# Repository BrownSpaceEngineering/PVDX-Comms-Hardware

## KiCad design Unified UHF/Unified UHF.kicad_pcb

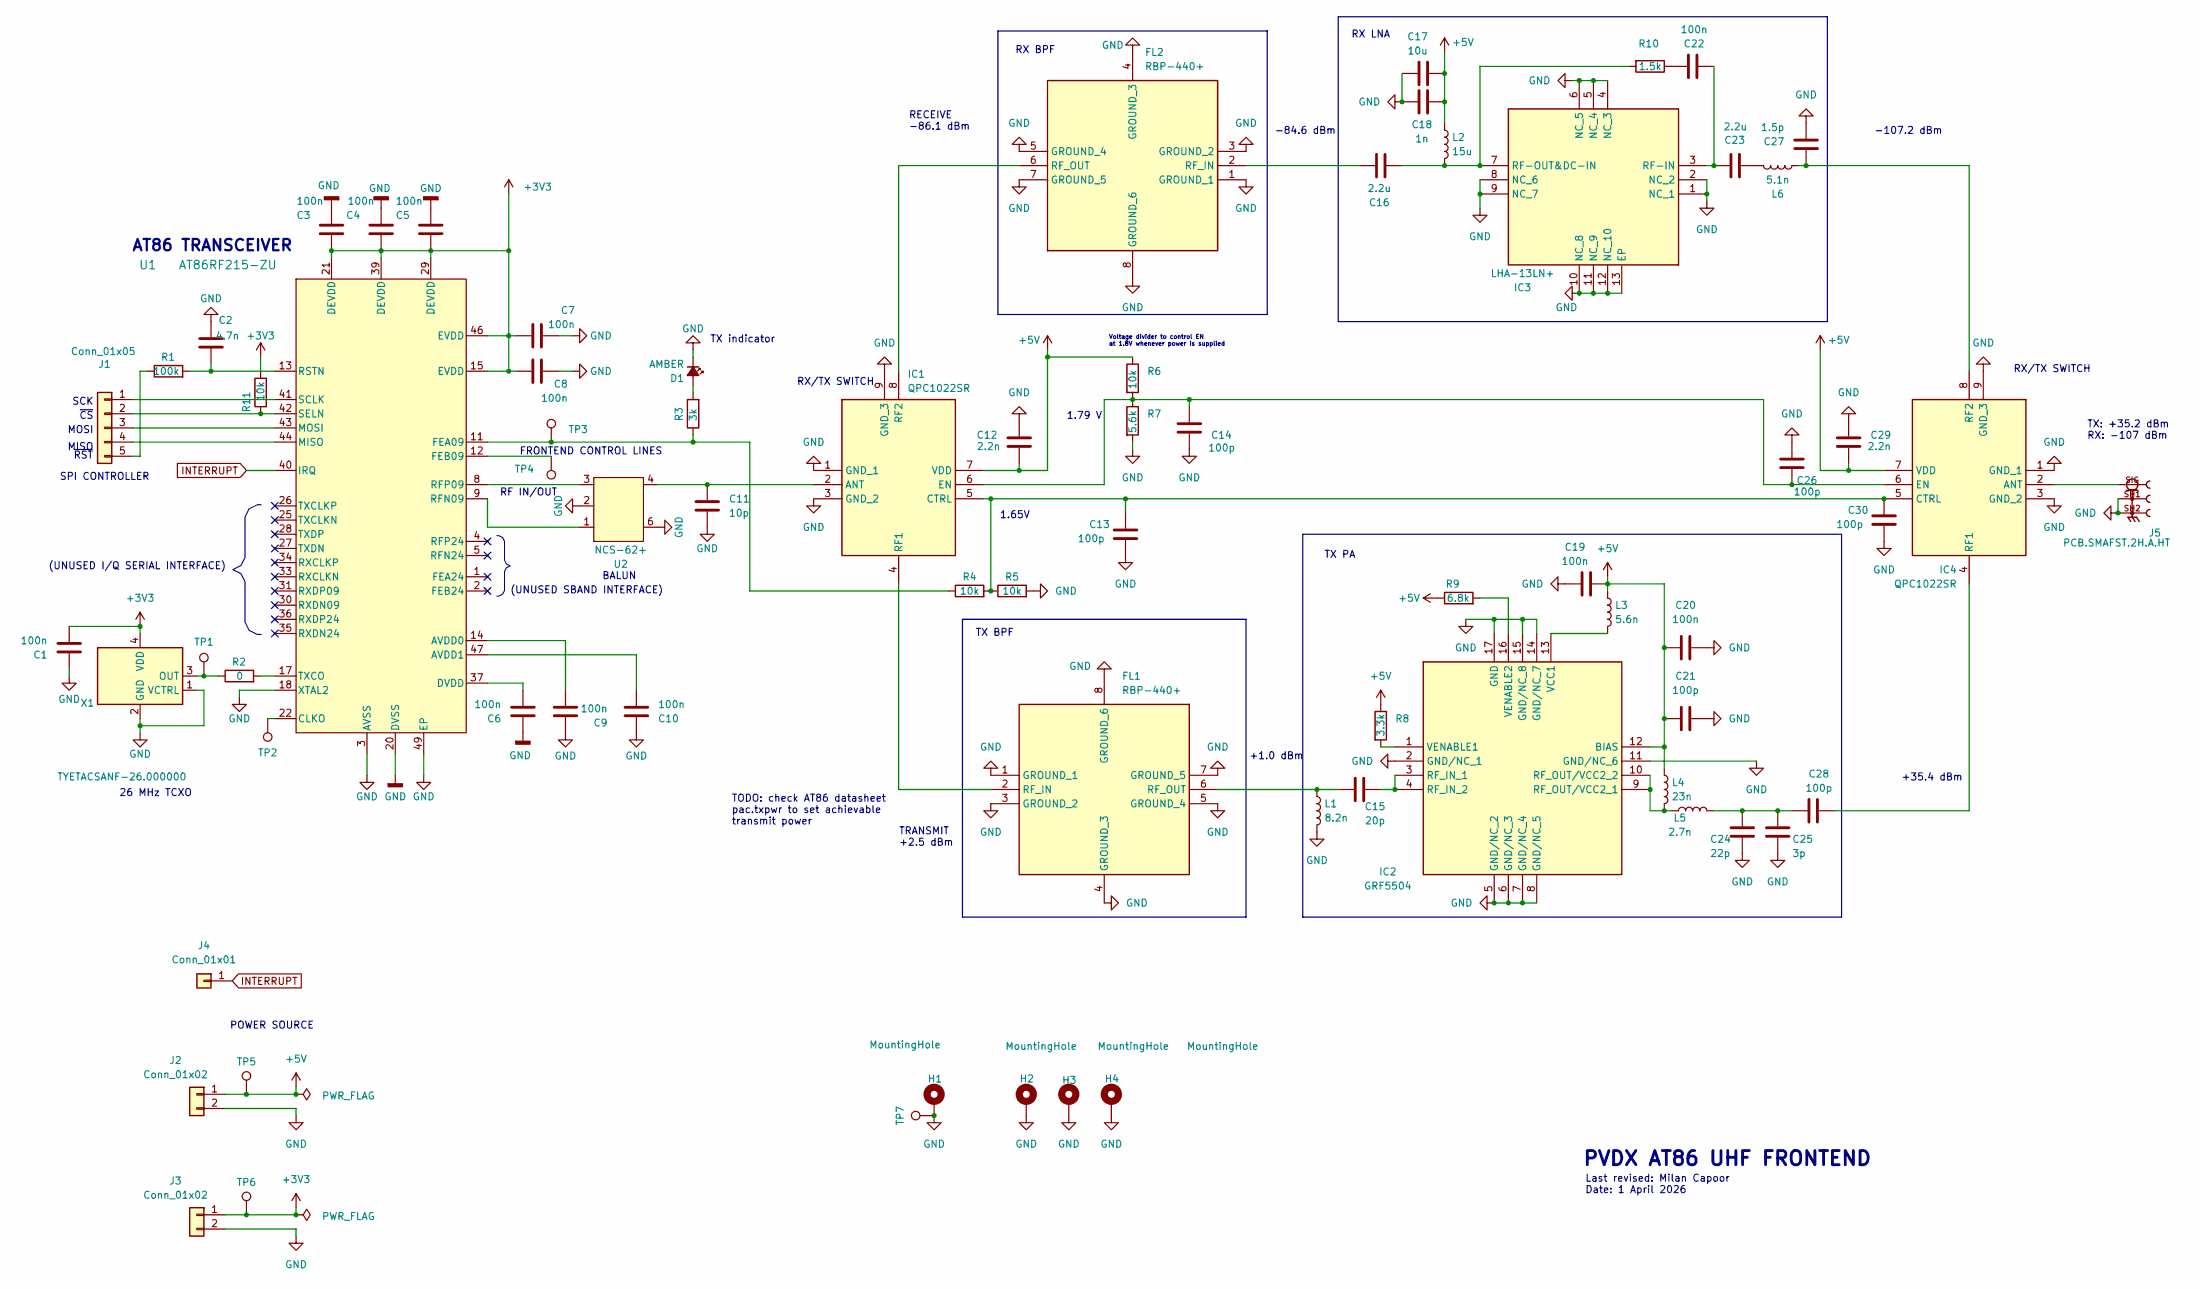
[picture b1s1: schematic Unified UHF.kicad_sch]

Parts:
C1, C3, C4, C5, C6, C7, C8, C9, C10, C19, C20, C22: 100n; C_0603_1608Metric
C2: 4.7n; C_0603_1608Metric
C11: 10p; C_0603_1608Metric
C12, C29: 2.2n; C_0603_1608Metric
C13, C14, C21, C26, C28, C30: 100p; C_0603_1608Metric
C15: 20p; C_0603_1608Metric
C16, C23: 2.2u; C_0603_1608Metric
C17: 10u; C_0805_2012Metric
C18: 1n; C_0603_1608Metric
C24: 22p; C_0603_1608Metric
C25: 3p; C_0603_1608Metric
C27: 1.5p; C_0603_1608Metric
D1: AMBER; LED_0603_1608Metric; MPN 150060AS75000
FL1, FL2: RBP-440+; RBP440; Mouser Part Number 139-RBP-440
H1, H2, H3, H4: MountingHole; MountingHole_3.4mm_Pad(edited from 3.5mm hole)
IC1, IC4: QPC1022SR; Mouser Part Number 772-QPC1022SR
IC2: GRF5504; GR5504; Mouser Part Number 459-GRF5504
IC3: LHA-13LN+; LHA13LN; Mouser Part Number 139-LHA-13LN
J1: Conn_01x05; PinSocket_1x05_P2.54mm_Vertical
J2, J3: Conn_01x02; PinSocket_1x02_P2.54mm_Vertical
J4: Conn_01x01; PinSocket_1x01_P2.54mm_Vertical
J5: PCB.SMAFST.2H.A.HT; TAOGLAS_PCB.SMAFST.2H.A.HT; PARTREV SPE-12-8-140/A/WY; DigiKey_Part_Number 931-1178-ND
L1: 8.2n; L_0603_1608Metric
L2: 15u; L_1210_3225Metric
L3: 5.6n; L_0805_2012Metric
L4: 23n; L_0805_2012Metric
L5: 2.7n; L_0603_1608Metric
L6: 5.1n; L_0603_1608Metric
R1: 100k; R_0603_1608Metric
R2: 0; R_0603_1608Metric
R3: 3k; R_0603_1608Metric
R4, R5, R6, R11: 10k; R_0603_1608Metric
R7: 5.6k; R_0603_1608Metric
R8: 3.3k; R_0603_1608Metric
R9: 6.8k; R_0603_1608Metric
R10: 1.5k; R_0603_1608Metric
TP1, TP2, TP3, TP4, TP5, TP6: TestPoint; TestPoint_Pad_D1.0mm
TP7: TestPoint; TestPoint_THTPad_D1.5mm_Drill0.7mm
U1: AT86RF215-ZU; AT86Footprint
U2: NCS-62+; NCS262
X1: TYETACSANF-26.000000; X_TCXO_SMD_Taitien_2.5x2.0mm; MPN TYETACSANF-26.000000

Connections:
+3V3: C1.2, C3.2, C4.2, C5.2, C7.2, C8.2, J3.1, R11.2, TP6.1 (1_1), U1.15 (EVDD), U1.21 (DEVDD), U1.29 (DEVDD), U1.39 (DEVDD), U1.46 (EVDD), X1.4 (VDD)
+5V: C12.1, C17.1, C18.1, C19.2, C20.1, C21.1, C29.1, IC1.7 (VDD), IC2.12 (BIAS), IC4.7 (VDD), J2.1, L2.1, L3.1, L4.1, R6.1, R8.1, R9.1, TP5.1 (1_1)
GND: C1.1, C2.1, C3.1, C4.1, C5.1, C6.1, C7.1, C8.1, C9.1, C10.1, C11.1, C12.2, C13.2, C14.2, C17.2, C18.2, C19.1, C20.2, C21.2, C24.2, C25.2, C26.2, C27.2, C29.2, C30.2, D1.1 (K), FL1.1 (GROUND_1), FL1.3 (GROUND_2), FL1.4 (GROUND_3), FL1.5 (GROUND_4), FL1.7 (GROUND_5), FL1.8 (GROUND_6), FL2.1 (GROUND_1), FL2.3 (GROUND_2), FL2.4 (GROUND_3), FL2.5 (GROUND_4), FL2.7 (GROUND_5), FL2.8 (GROUND_6), H1.1 (1_1), H2.1 (1_1), H3.1 (1_1), H4.1 (1_1), IC1.1 (GND_1), IC1.3 (GND_2), IC1.9 (GND_3), IC2.2 (GND/NC_1), IC2.5 (GND/NC_2), IC2.6 (GND/NC_3), IC2.7 (GND/NC_4), IC2.8 (GND/NC_5), IC2.11 (GND/NC_6), IC2.14 (GND/NC_7), IC2.15 (GND/NC_8), IC2.17 (GND), IC3.1 (NC_1), IC3.2 (NC_2), IC3.4 (NC_3), IC3.5 (NC_4), IC3.6 (NC_5), IC3.8 (NC_6), IC3.9 (NC_7), IC3.10 (NC_8), IC3.11 (NC_9), IC3.12 (NC_10), IC3.13 (EP), IC4.1 (GND_1), IC4.3 (GND_2), IC4.9 (GND_3), J2.2, J3.2, J5.SH1, J5.SH2, L1.2, R5.2, R7.2, TP7.1 (1_1), U1.3 (AVSS), U1.6 (AVSS), U1.7 (AVSS), U1.10 (AVSS), U1.16 (AVSS), U1.18 (XTAL2), U1.19 (AVSS), U1.20 (DVSS), U1.23 (DVSS), U1.24 (DVSS), U1.32 (DVSS), U1.38 (DVSS), U1.45 (AVSS), U1.48 (AVSS), U1.49 (EP), U2.2, U2.6, X1.1 (VCTRL), X1.2 (GND)
INTERRUPT: J4.1 (Pin_1_1), U1.40 (IRQ)
unnamed: C22.2, R10.1
unnamed: C23.1, L6.2
unnamed: C24.1, C25.1, C28.1, L5.2
unnamed: D1.2 (A), R3.2
unnamed: FL1.2 (RF_IN), IC1.4 (RF1)
unnamed: C15.1, FL1.6 (RF_OUT), L1.1
unnamed: C16.2, FL2.2 (RF_IN)
unnamed: FL2.6 (RF_OUT), IC1.8 (RF2)
unnamed: C11.2, IC1.2 (ANT), U2.4
unnamed: C13.1, C30.1, IC1.5 (CTRL), IC4.5 (CTRL), R4.2, R5.1
unnamed: C14.1, C26.1, IC1.6 (EN), IC4.6 (EN), R6.2, R7.1
unnamed: C15.2, IC2.3 (RF_IN_1), IC2.4 (RF_IN_2)
unnamed: IC2.9 (RF_OUT/VCC2_1), IC2.10 (RF_OUT/VCC2_2), L4.2, L5.1
unnamed: IC2.13 (VCC1), L3.2
unnamed: IC2.1 (VENABLE1), R8.2
unnamed: IC2.16 (VENABLE2), R9.2
unnamed: C22.1, C23.2, IC3.3 (RF-IN)
unnamed: C16.1, IC3.7 (RF-OUT&DC-IN), L2.2, R10.2
unnamed: IC4.2 (ANT), J5.SIG
unnamed: C28.2, IC4.4 (RF1)
unnamed: C27.1, IC4.8 (RF2), L6.1
unnamed: J1.1, U1.41 (SCLK)
unnamed: J1.2, R11.1, U1.42 (SELN)
unnamed: J1.3, U1.43 (MOSI)
unnamed: J1.4, U1.44 (MISO)
unnamed: J1.5, R1.1
unnamed: C9.2, U1.14 (AVDD0)
unnamed: C10.2, U1.47 (AVDD1)
unnamed: TP2.1 (1_1), U1.22 (CLKO)
unnamed: C6.2, U1.37 (DVDD)
unnamed: R3.1, R4.1, TP3.1 (1_1), U1.11 (FEA09)
unnamed: TP4.1 (1_1), U1.12 (FEB09)
unnamed: U1.9 (RFN09), U2.1
unnamed: U1.8 (RFP09), U2.3
unnamed: C2.2, R1.2, U1.13 (RSTN)
unnamed: R2.2, U1.17 (TXCO)
unnamed: R2.1, TP1.1 (1_1), X1.3 (OUT)

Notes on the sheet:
SCK
(UNUSED SBAND INTERFACE)
MISO
TX PA
RX BPF
~{CS}
FRONTEND CONTROL LINES
RX/TX SWITCH
BALUN
SPI CONTROLLER
TRANSMIT +2.5 dBm
TX BPF
+35.4 dBm
-107.2 dBm
-84.6 dBm
1.65V
~{RST}
TX indicator
TODO: check AT86 datasheet pac.txpwr to set achievable transmit power
1.79 V
RF IN/OUT
RECEIVE -86.1 dBm
Last revised: Milan Capoor Date: 1 April 2026
RX LNA
26 MHz TCXO
Voltage divider to control EN at 1.8V whenever power is supplied
(UNUSED I/Q SERIAL INTERFACE)
+1.0 dBm
AT86 TRANSCEIVER
MOSI
PVDX AT86 UHF FRONTEND
POWER SOURCE
TX: +35.2 dBm RX: -107 dBm

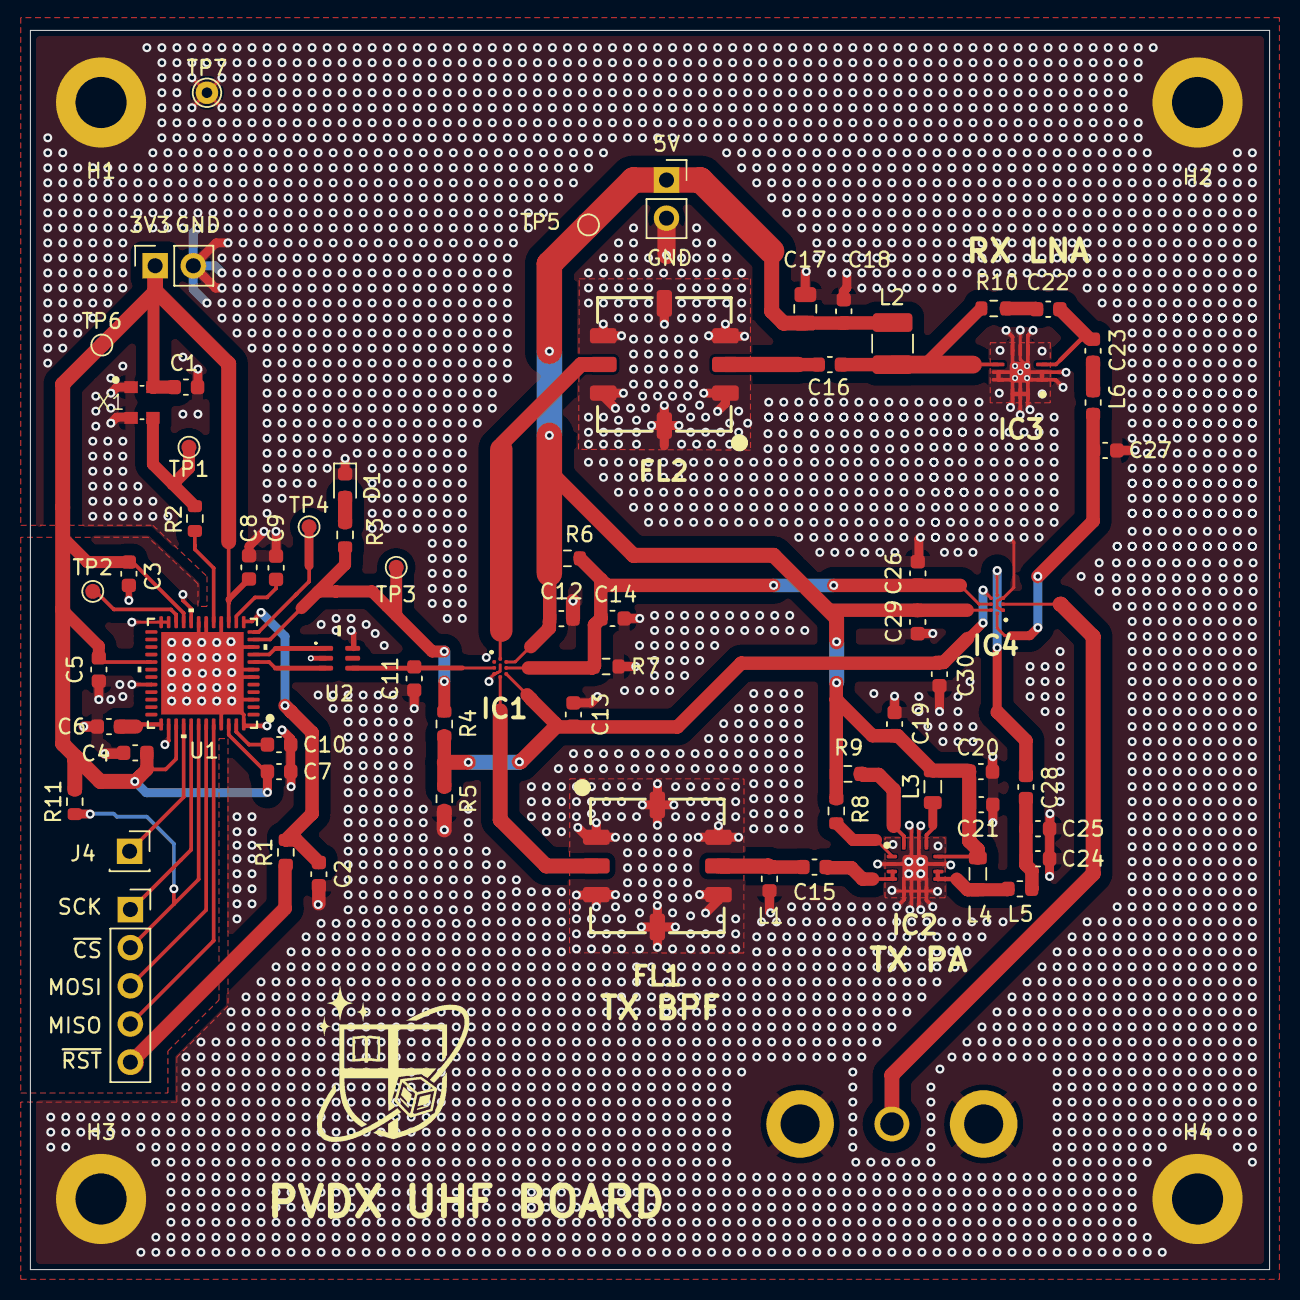
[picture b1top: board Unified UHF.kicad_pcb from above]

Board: 2 copper layers, 82.5 x 82.5 mm, 73 parts (1 on the bottom side), 41 nets.

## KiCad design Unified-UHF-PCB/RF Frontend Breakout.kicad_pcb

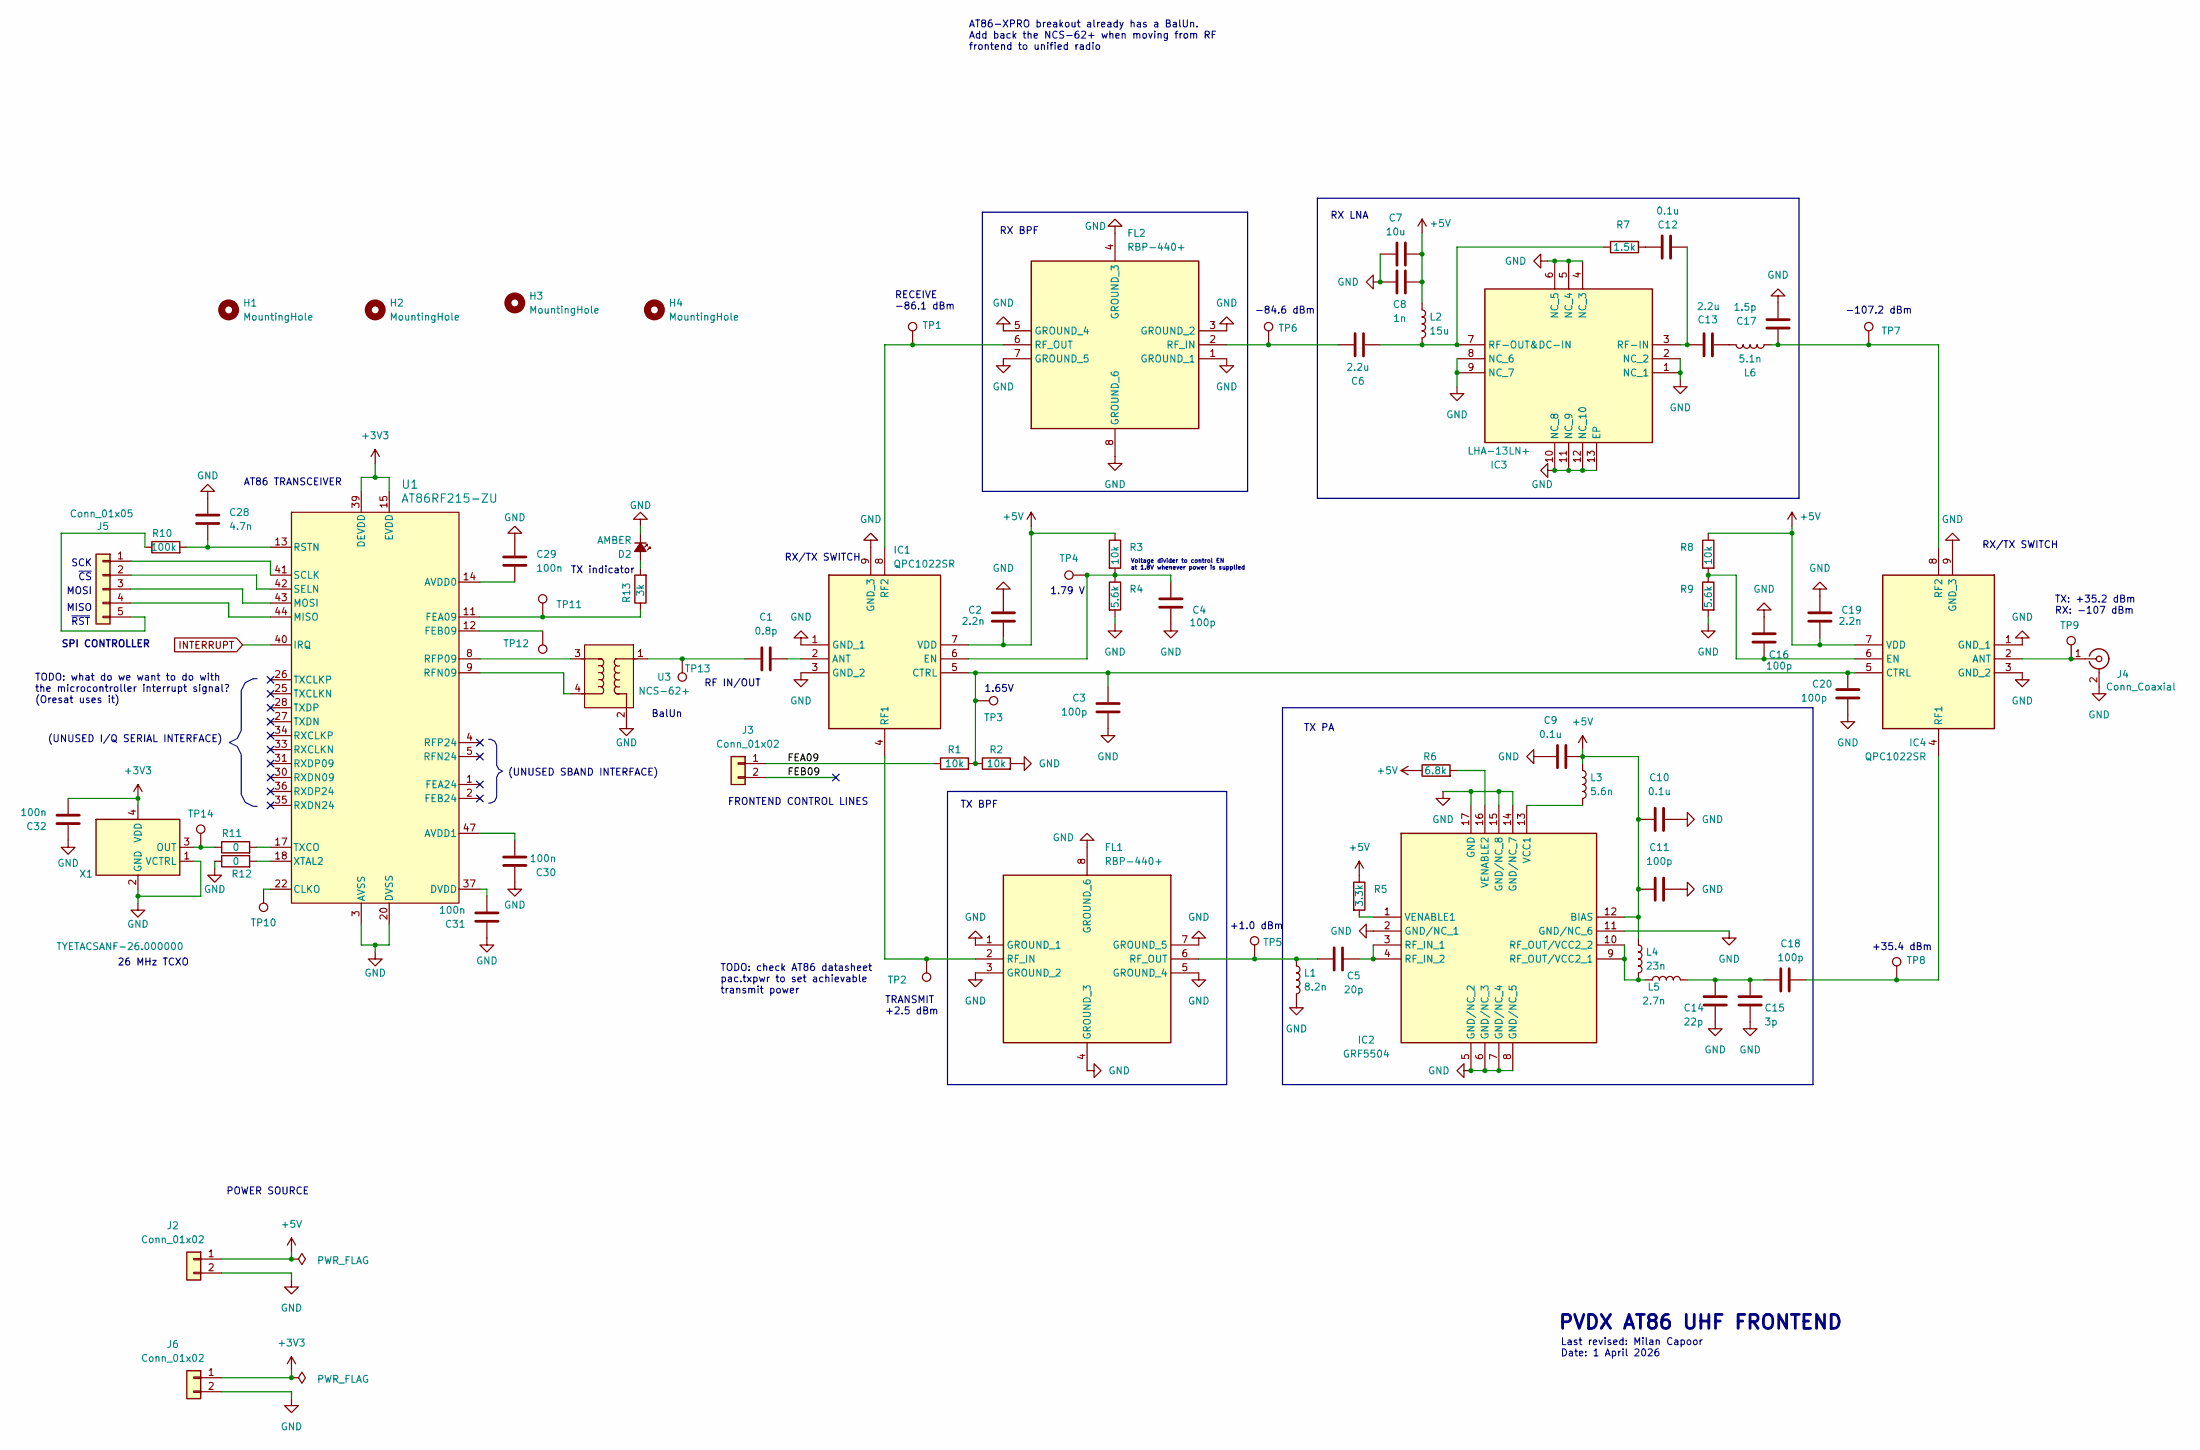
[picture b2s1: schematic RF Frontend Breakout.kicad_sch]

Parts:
C1: 0.8p; C_0603_1608Metric
C2, C19: 2.2n; C_0603_1608Metric
C3, C4, C11, C16, C18, C20: 100p; C_0603_1608Metric
C5: 20p; C_0603_1608Metric
C6, C13: 2.2u; C_0603_1608Metric
C7: 10u; C_0805_2012Metric
C8: 1n; C_0603_1608Metric
C9, C10, C12: 0.1u; C_0603_1608Metric
C14: 22p; C_0603_1608Metric
C15: 3p; C_0603_1608Metric
C17: 1.5p; C_0603_1608Metric
C28: 4.7n; C_0603_1608Metric
C29, C30, C31, C32: 100n; C_0603_1608Metric
D2: AMBER; LED_0603_1608Metric; MPN 150060AS75000
FL1, FL2: RBP-440+; RBP440; Mouser Part Number 139-RBP-440
H1, H2, H3, H4: MountingHole; MountingHole_3.2mm_M3
IC1, IC4: QPC1022SR; Mouser Part Number 772-QPC1022SR
IC2: GRF5504; GR5504; Mouser Part Number 459-GRF5504
IC3: LHA-13LN+; LHA13LN; Mouser Part Number 139-LHA-13LN
J2, J3, J6: Conn_01x02; PinSocket_1x02_P2.54mm_Vertical
J4: Conn_Coaxial; SMA_Molex_73251-1153_EdgeMount_Horizontal
J5: Conn_01x05; PinSocket_1x05_P2.54mm_Vertical
L1: 8.2n; L_0603_1608Metric
L2: 15u; L_1210_3225Metric
L3: 5.6n; L_0805_2012Metric
L4: 23n; L_0805_2012Metric
L5: 2.7n; L_0603_1608Metric
L6: 5.1n; L_0603_1608Metric
R1, R2, R3, R8: 10k; R_0603_1608Metric
R4, R9: 5.6k; R_0603_1608Metric
R5: 3.3k; R_0603_1608Metric
R6: 6.8k; R_0603_1608Metric
R7: 1.5k; R_0603_1608Metric
R10: 100k; R_0603_1608Metric
R11, R12: 0; R_0603_1608Metric
R13: 3k; R_0603_1608Metric
TP1, TP2, TP3, TP4, TP5, TP6, TP7, TP8, TP9, TP10, TP11, TP12, TP13, TP14: TestPoint; TestPoint_THTPad_1.5x1.5mm_Drill0.7mm
U1: AT86RF215-ZU; QFN-48-1EP_7x7mm_P0.5mm_EP5.6x5.6mm
U3: NCS-62+; NCS262
X1: TYETACSANF-26.000000; X_TCXO_SMD_Taitien_2.5x2.0mm; MPN TYETACSANF-26.000000

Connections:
+3V3: C32.2, J6.1, U1.15 (EVDD), U1.39 (DEVDD), X1.4 (VDD)
+5V: C2.1, C7.1, C8.1, C9.2, C10.1, C11.1, C19.1, IC1.7 (VDD), IC2.12 (BIAS), IC4.7 (VDD), J2.1, L2.1, L3.1, L4.1, R3.1, R5.1, R6.1, R8.1
/FEA09: J3.1, R1.1
/FEB09: J3.2
GND: C2.2, C3.2, C4.2, C7.2, C8.2, C9.1, C10.2, C11.2, C14.2, C15.2, C16.2, C17.2, C19.2, C20.2, C28.1, C29.1, C30.1, C31.1, C32.1, D2.1 (K), FL1.1 (GROUND_1), FL1.3 (GROUND_2), FL1.4 (GROUND_3), FL1.5 (GROUND_4), FL1.7 (GROUND_5), FL1.8 (GROUND_6), FL2.1 (GROUND_1), FL2.3 (GROUND_2), FL2.4 (GROUND_3), FL2.5 (GROUND_4), FL2.7 (GROUND_5), FL2.8 (GROUND_6), IC1.1 (GND_1), IC1.3 (GND_2), IC1.9 (GND_3), IC2.2 (GND/NC_1), IC2.5 (GND/NC_2), IC2.6 (GND/NC_3), IC2.7 (GND/NC_4), IC2.8 (GND/NC_5), IC2.11 (GND/NC_6), IC2.14 (GND/NC_7), IC2.15 (GND/NC_8), IC2.17 (GND), IC3.1 (NC_1), IC3.2 (NC_2), IC3.4 (NC_3), IC3.5 (NC_4), IC3.6 (NC_5), IC3.8 (NC_6), IC3.9 (NC_7), IC3.10 (NC_8), IC3.11 (NC_9), IC3.12 (NC_10), IC3.13 (EP), IC4.1 (GND_1), IC4.3 (GND_2), IC4.9 (GND_3), J2.2, J4.2 (Ext), J6.2, L1.2, R2.2, R4.2, R9.2, R12.1, U1.3 (AVSS), U1.20 (DVSS), U3.2, X1.1 (VCTRL), X1.2 (GND)
INTERRUPT: U1.40 (IRQ)
unnamed: C1.1, TP13.1 (1_1), U3.1
unnamed: C12.2, R7.1
unnamed: C13.1, L6.2
unnamed: C14.1, C15.1, C18.1, L5.2
unnamed: D2.2 (A), R13.2
unnamed: FL1.2 (RF_IN), IC1.4 (RF1), TP2.1 (1_1)
unnamed: C5.1, FL1.6 (RF_OUT), L1.1, TP5.1 (1_1)
unnamed: C6.2, FL2.2 (RF_IN), TP6.1 (1_1)
unnamed: FL2.6 (RF_OUT), IC1.8 (RF2), TP1.1 (1_1)
unnamed: C1.2, IC1.2 (ANT)
unnamed: C3.1, C20.1, IC1.5 (CTRL), IC4.5 (CTRL), R1.2, R2.1, TP3.1 (1_1)
unnamed: C4.1, IC1.6 (EN), R3.2, R4.1, TP4.1 (1_1)
unnamed: C5.2, IC2.3 (RF_IN_1), IC2.4 (RF_IN_2)
unnamed: IC2.9 (RF_OUT/VCC2_1), IC2.10 (RF_OUT/VCC2_2), L4.2, L5.1
unnamed: IC2.13 (VCC1), L3.2
unnamed: IC2.1 (VENABLE1), R5.2
unnamed: IC2.16 (VENABLE2), R6.2
unnamed: C12.1, C13.2, IC3.3 (RF-IN)
unnamed: C6.1, IC3.7 (RF-OUT&DC-IN), L2.2, R7.2
unnamed: IC4.2 (ANT), J4.1 (In), TP9.1 (1_1)
unnamed: C16.1, IC4.6 (EN), R8.2, R9.1
unnamed: C18.2, IC4.4 (RF1), TP8.1 (1_1)
unnamed: C17.1, IC4.8 (RF2), L6.1, TP7.1 (1_1)
unnamed: J5.1, U1.41 (SCLK)
unnamed: J5.2, U1.42 (SELN)
unnamed: J5.3, U1.43 (MOSI)
unnamed: J5.4, U1.44 (MISO)
unnamed: J5.5, R10.1
unnamed: C29.2, U1.14 (AVDD0)
unnamed: C30.2, U1.47 (AVDD1)
unnamed: TP10.1 (1_1), U1.22 (CLKO)
unnamed: C31.2, U1.37 (DVDD)
unnamed: R13.1, TP11.1 (1_1), U1.11 (FEA09)
unnamed: TP12.1 (1_1), U1.12 (FEB09)
unnamed: U1.9 (RFN09), U3.4
unnamed: U1.8 (RFP09), U3.3
unnamed: C28.2, R10.2, U1.13 (RSTN)
unnamed: R11.2, U1.17 (TXCO)
unnamed: R12.2, U1.18 (XTAL2)
unnamed: R11.1, TP14.1 (1_1), X1.3 (OUT)

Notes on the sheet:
SCK
(UNUSED SBAND INTERFACE)
AT86-XPRO breakout already has a BalUn. Add back the NCS-62+ when moving from RF frontend to unified radio
MISO
TX PA
RX BPF
~{CS}
FRONTEND CONTROL LINES
RX/TX SWITCH
BalUn
SPI CONTROLLER
TRANSMIT +2.5 dBm
TX BPF
+35.4 dBm
-107.2 dBm
-84.6 dBm
1.65V
TODO: what do we want to do with the microcontroller interrupt signal? (Oresat uses it)
~{RST}
TX indicator
TODO: check AT86 datasheet pac.txpwr to set achievable transmit power
1.79 V
RF IN/OUT
RECEIVE -86.1 dBm
Last revised: Milan Capoor Date: 1 April 2026
RX LNA
26 MHz TCXO
Voltage divider to control EN at 1.8V whenever power is supplied
(UNUSED I/Q SERIAL INTERFACE)
+1.0 dBm
AT86 TRANSCEIVER
MOSI
PVDX AT86 UHF FRONTEND
POWER SOURCE
TX: +35.2 dBm RX: -107 dBm

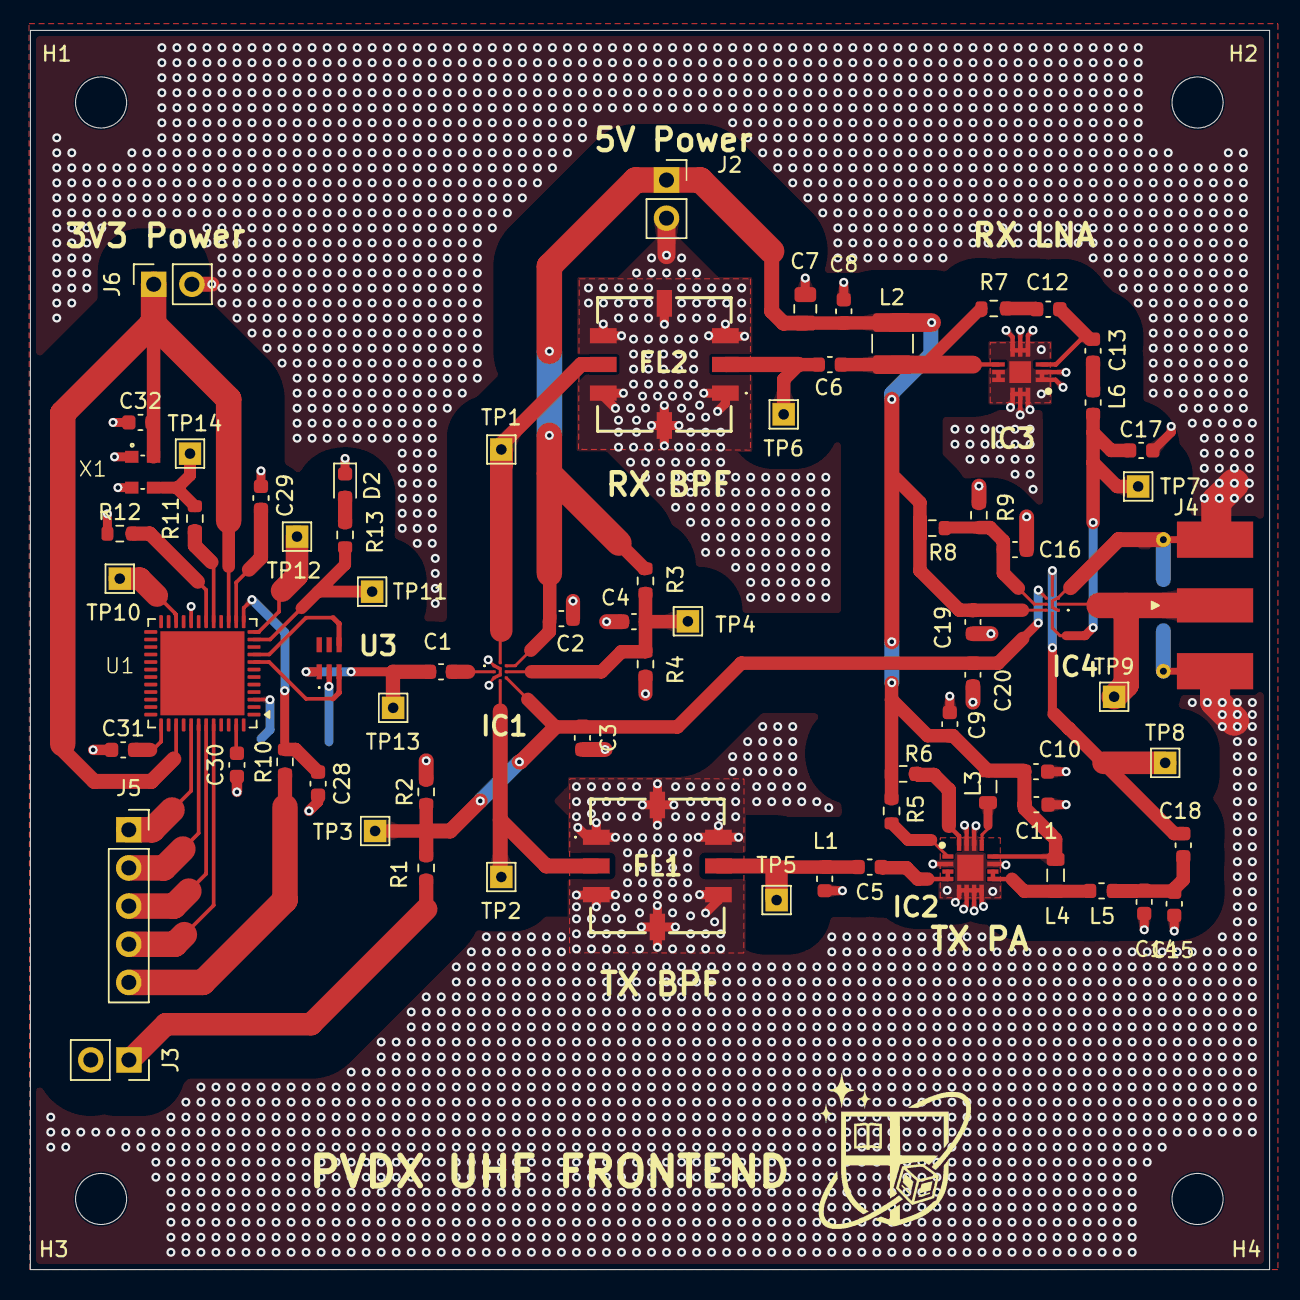
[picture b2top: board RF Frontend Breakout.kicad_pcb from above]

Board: 2 copper layers, 82.5 x 82.5 mm, 77 parts (0 on the bottom side), 44 nets.

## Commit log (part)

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2025-11-23 Initial schematic from datasheet
2025-11-23 Removed artifact readme contents about manufacturing tolerances
2026-04-01 rf frontend schematic initial commit
2026-04-01 reorganized component libraries
2026-04-05 tweaks
2026-04-06 tweaks to PA
2026-04-19 initial frontend layout
2026-05-01 test
2026-05-03 finished pcb
2026-05-07 small changes after larry meeting will populate his changes later
2026-05-10 added groundplate to BPF and vias
2026-05-21 brought power traces to front
